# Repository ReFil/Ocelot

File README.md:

# Ocelot
Ocelot universal vehicle interface

This is an in progress project aimed at creating a universal set of hardware intended to allow autonomous driving.
The hardware consists of a fly by wire pedal interceptor, a universal cruise controls emulator, reverse engineered white panda and black panda, canbus gateway board for iboosters or corolla EPS controllers and an interface board that ties everythign together
In the future we plan on a cable throttle actuator and a speed and pedal sensor to allow for fitting on cars without any electronics at all.

The software for most of the modules is based off the comma.ai panda firmware to take advantage of the safety and updating over CAN bus

Any user of this software/hardsware shall indemnify and hold harmless Willow Herring. and their associates from and against all allegations, claims, actions, suits, demands, damages, liabilities, obligations, losses, settlements, judgments, costs and expenses (including without limitation attorneys’ fees and costs) which arise out of, relate to or result from any use of this software by user.

THIS IS ALPHA QUALITY HARDWARE FOR RESEARCH PURPOSES ONLY. THIS IS NOT A PRODUCT. YOU ARE RESPONSIBLE FOR COMPLYING WITH LOCAL LAWS AND REGULATIONS. NO WARRANTY EXPRESSED OR IMPLIED
I AM NOT RESPONSIBLE FOR WORLD WAR 3, YOUR HOUSE BURNING DOWN OR YOU GETTING FIRED BECAUSE YOUR CAR BROKE DOWN ON THE WAY TO WORK, BY USING THIS HARDWARE/SOFTWARE YOU ASSUME RESPONSIBILITY FOR ALL CONSEQUENCES.

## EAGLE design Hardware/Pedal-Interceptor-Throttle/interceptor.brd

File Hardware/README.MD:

Hardware

The hardware is designed to be as easy to use as possible.

All can bus connections are made using molex mini50 4 pin connectors with A polarisation
The pinout is 12V CANH CANL GND from pin 1-4

The CAN interface board connects everything together, compatible with white, grey and black panda as well as c2

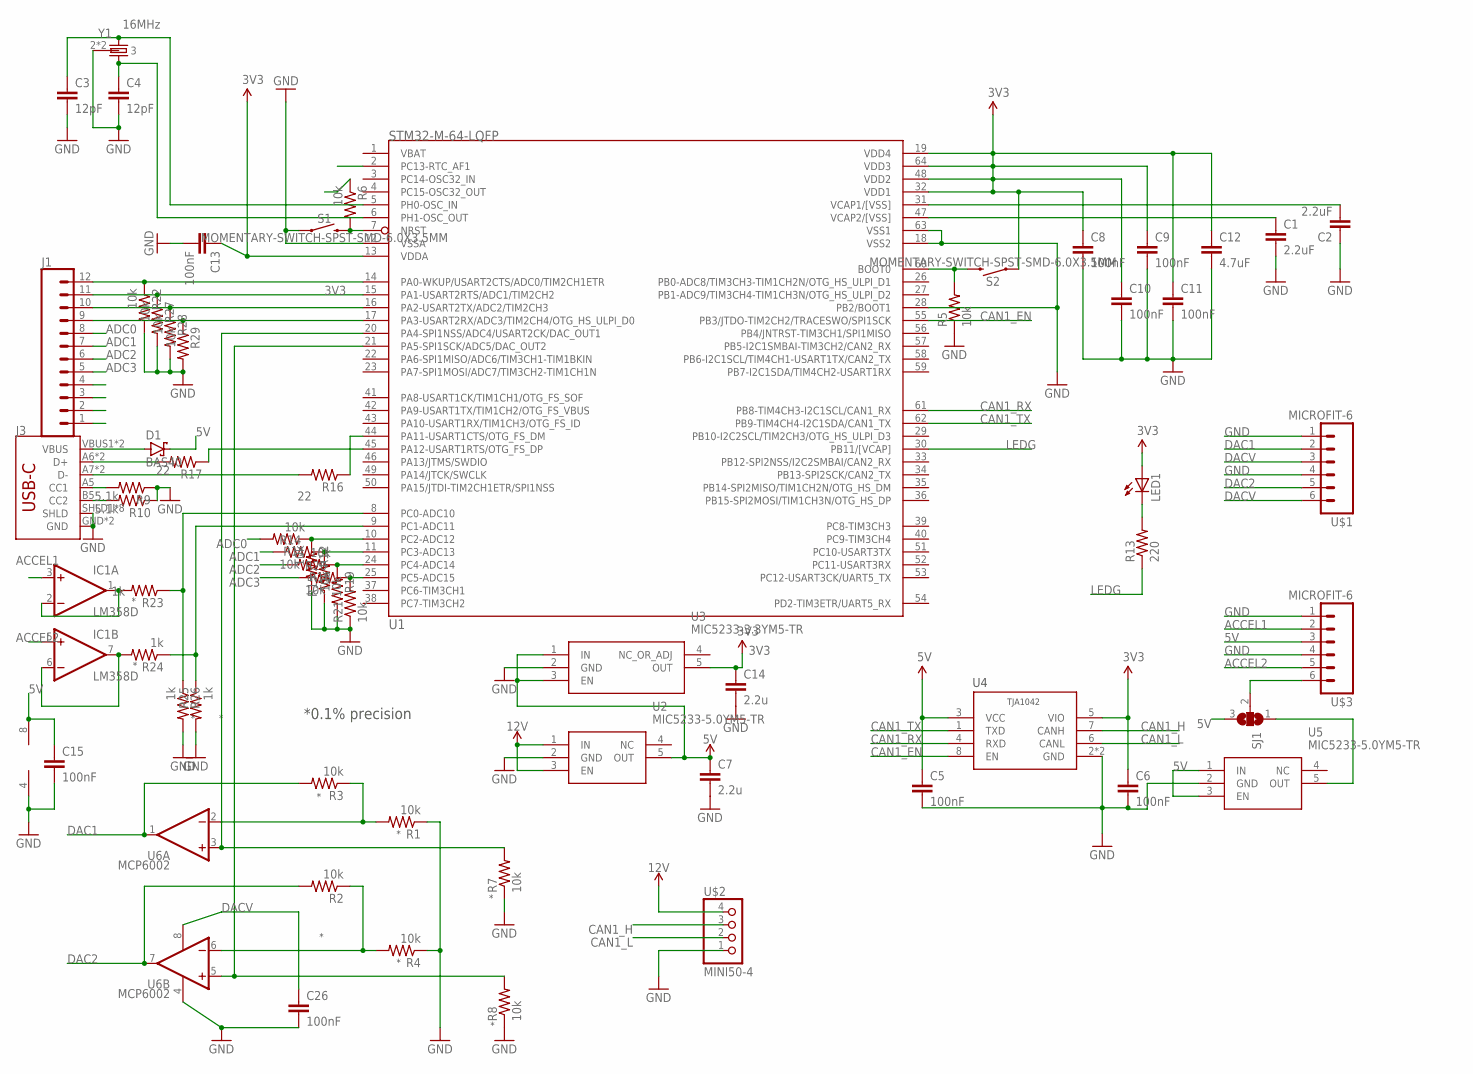
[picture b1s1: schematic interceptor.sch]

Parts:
C1, C2: 2.2uF; 0603-C
C3, C4: 12pF; 0603-C
C5, C6, C8, C9, C10, C11, C13, C15, C26: 100nF; 0603-C
C7, C14: 2.2u; C0603
C12: 4.7uF; 0603-C
D1: BAS40; SOT23
IC1: LM358D; SO08
J1: CONN_12; 1X12
J3: USB-C-BREAKOUT_SPARKFUN-CONNECTORS_USB_C16PIN; USB-C-BREAKOUT_SPARKFUN-CONNECTORS_USB-C-16P
LED1: LEDCHIPLED_0805; CHIPLED_0805
R1, R2, R3, R4, R5, R6, R7, R8, R11, R12, R14, R15, R18, R19, R20, R21, R22, R27, R28, R29: 10k; 0402-R
R9, R10: 5.1k; 0402-R
R13: 220; 0402-R
R16, R17: 22; 0402-R
R23, R24, R25, R26: 1k; 0402-R
S1, S2: MOMENTARY-SWITCH-SPST-SMD-6.0X3.5MM; TACTILE_SWITCH_SMD_6.0X3.5MM
SJ1: SJ2W; SJ_2
U1: STM32-M-64-LQFP; LQFP64
U2, U5: MIC5233-5.0YM5-TR; SOT95P280X145-5N
U3: MIC5233-3.3YM5-TR; SOT95P280X145-5N
U4: TJA1042HVSON; HVSON8
U6: MCP6002; SO08
U$1, U$3: MICROFIT-6
U$2: MINI50-4; MINI50
Y1: 16MHz; XTAL-3.2X2.5

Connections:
3V3: C6.1, C8.1, C9.1, C10.1, C11.1, C12.1, C13.1, C14.1, LED1.A, R6.1, S2.1, U1.13 (VDDA), U1.19 (VDD4), U1.32 (VDD1), U1.48 (VDD2), U1.64 (VDD3), U3.5 (OUT), U4.5 (VIO)
5V: C5.1, C7.1, C15.1, D1.3 (C), IC1.8 (V+), SJ1.3, U2.5 (OUT), U3.1 (IN), U3.3 (EN), U4.3 (VCC), U5.1 (IN), U5.3 (EN), U$3.3
12V: U2.1 (IN), U2.3 (EN), U$2.4 (1)
ACCEL1: IC1.3 (+IN), U$3.2
ACCEL2: IC1.5 (+IN), U$3.5
ADC0: J1.8, R11.2
ADC1: J1.7, R14.1
ADC2: J1.6, R18.2
ADC3: J1.5, R20.1
CAN1_EN: U1.55 (PB3/JTDO-TIM2CH2/TRACESWO/SPI1SCK), U4.8 (EN)
CAN1_H: U4.7 (CANH), U$2.3 (2)
CAN1_L: U4.6 (CANL), U$2.2 (3)
CAN1_RX: U1.61 (PB8-TIM4CH3-I2C1SCL/CAN1_RX), U4.4 (RXD)
CAN1_TX: U1.62 (PB9-TIM4CH4-I2C1SDA/CAN1_TX), U4.1 (TXD)
DAC1: R3.2, U6.1 (OUT), U$1.2
DAC2: R2.2, U6.7 (OUT), U$1.5
DACV: C26.1, U6.8 (V+), U$1.3, U$1.6
GND: C1.2, C2.1, C3.2, C4.2, C5.2, C6.2, C7.2, C8.2, C9.2, C10.2, C11.2, C12.2, C13.2, C14.2, C15.2, C26.2, IC1.4 (V-), J3.GND, J3.GND2 (GND), J3.SHLD1 (SHLD), J3.SHLD2 (SHLD), J3.SHLD3 (SHLD), J3.SHLD4 (SHLD), J3.SHLD5 (SHLD), J3.SHLD6 (SHLD), J3.SHLD7 (SHLD), J3.SHLD8 (SHLD), R1.1, R4.1, R5.1, R7.1, R8.1, R9.1, R10.1, R12.2, R15.1, R19.2, R21.1, R22.2, R25.2, R26.2, R27.2, R28.2, R29.2, S1.1, U1.12 (VSSA), U1.18 (VSS2), U1.28 (PB2/BOOT1), U1.63 (VSS1), U2.2 (GND), U3.2 (GND), U4.2 (GND), U4.PAD (GND), U5.2 (GND), U6.4 (V-), U$1.1, U$1.4, U$2.1 (4), U$3.1, U$3.4, Y1.2 (3), Y1.4 (3)
LEDG: R13.1, U1.30 (PB11/[VCAP])
unnamed: C3.1, U1.5 (PH0-OSC_IN), Y1.1
unnamed: R16.1, U1.44 (PA11-USART1CTS/OTG_FS_DM)
unnamed: C4.1, U1.6 (PH1-OSC_OUT), Y1.3 (2)
unnamed: R17.1, U1.45 (PA12-USART1RTS/OTG_FS_DP)
unnamed: J3.A7 (D-), J3.B7 (D-), R16.2
unnamed: J3.A6 (D+), J3.B6 (D+), R17.2
unnamed: R5.2, S2.2, U1.60 (BOOT0)
unnamed: J3.A5 (CC1), R9.2
unnamed: J3.B5 (CC2), R10.2
unnamed: R6.2, S1.2, U1.7 (NRST)
unnamed: D1.1 (A), J3.VBUS1 (VBUS), J3.VBUS2 (VBUS)
unnamed: SJ1.2, U$3.6
unnamed: IC1.1 (OUT), IC1.2 (-IN), R23.2
unnamed: SJ1.1, U5.5 (OUT)
unnamed: IC1.6 (-IN), IC1.7 (OUT), R24.2
unnamed: R11.1, R12.1, U1.10 (PC2-ADC12)
unnamed: R7.2, U1.20 (PA4-SPI1NSS/ADC4/USART2CK/DAC_OUT1), U6.3 (+IN)
unnamed: R8.2, U1.21 (PA5-SPI1SCK/ADC5/DAC_OUT2), U6.5 (+IN)
unnamed: R14.2, R15.2, U1.11 (PC3-ADC13)
unnamed: R18.1, R19.1, U1.24 (PC4-ADC14)
unnamed: R1.2, R3.1, U6.2 (-IN)
unnamed: R2.1, R4.2, U6.6 (-IN)
unnamed: R20.2, R21.2, U1.25 (PC5-ADC15)
unnamed: LED1.C, R13.2
unnamed: J1.9, R29.1, U1.17 (PA3-USART2RX/ADC3/TIM2CH4/OTG_HS_ULPI_D0)
unnamed: J1.10, R28.1, U1.16 (PA2-USART2TX/ADC2/TIM2CH3)
unnamed: J1.11, R27.1, U1.15 (PA1-USART2RTS/ADC1/TIM2CH2)
unnamed: J1.12, R22.1, U1.14 (PA0-WKUP/USART2CTS/ADC0/TIM2CH1ETR)
unnamed: R23.1, R26.1, U1.8 (PC0-ADC10)
unnamed: R24.1, R25.1, U1.9 (PC1-ADC11)
VCAP1: C2.2, U1.31 (VCAP1/[VSS])
VCAP2: C1.1, U1.47 (VCAP2/[VSS])

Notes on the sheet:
*0.1% precision

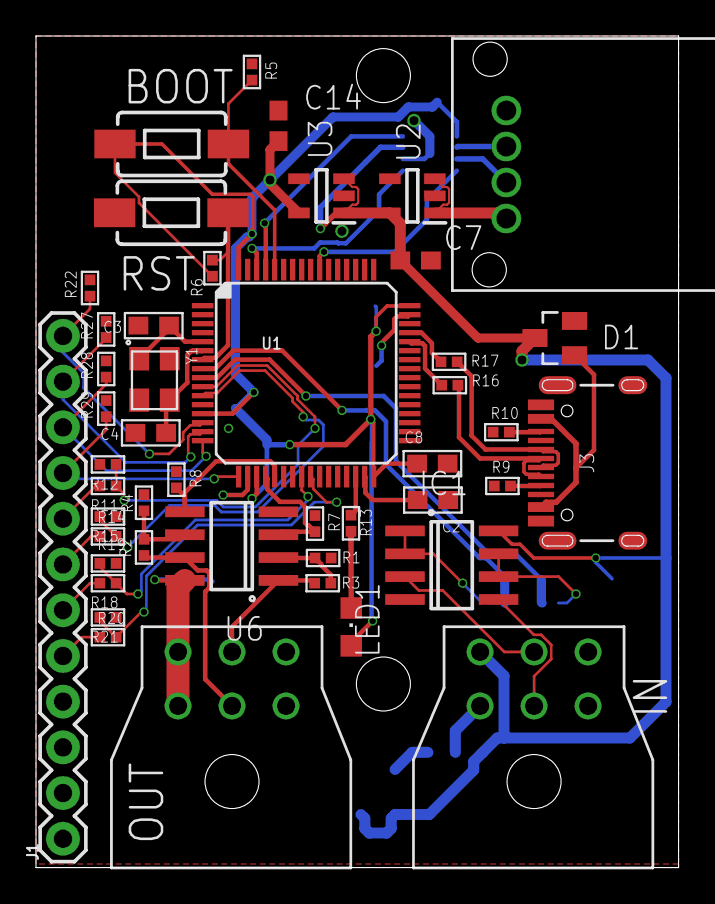
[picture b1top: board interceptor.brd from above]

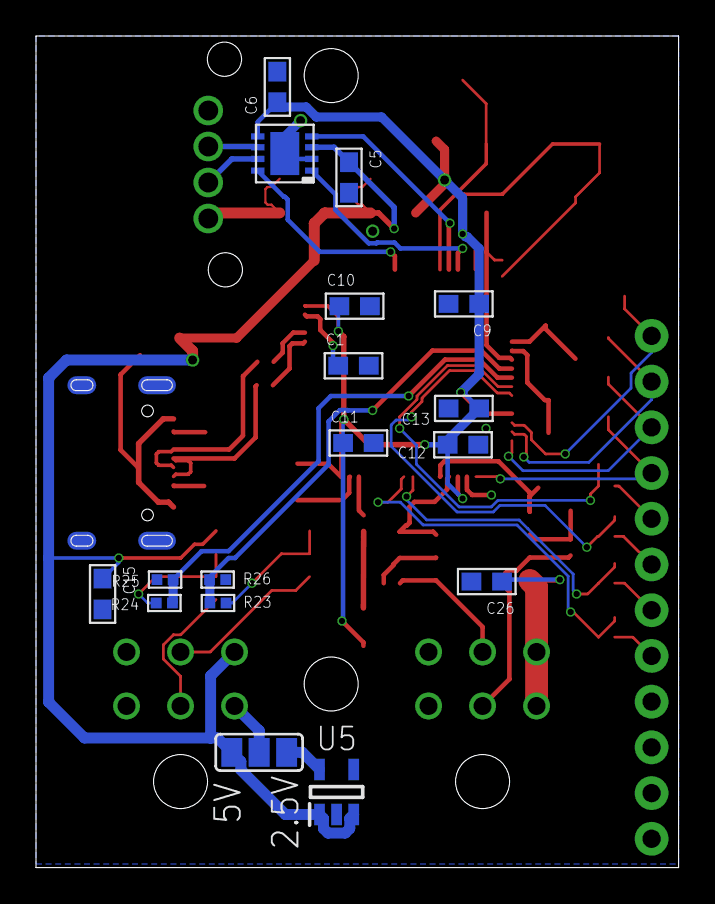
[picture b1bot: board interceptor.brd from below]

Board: 2 copper layers, 35.7 x 46.2 mm, 63 parts (17 on the bottom side), 51 nets.

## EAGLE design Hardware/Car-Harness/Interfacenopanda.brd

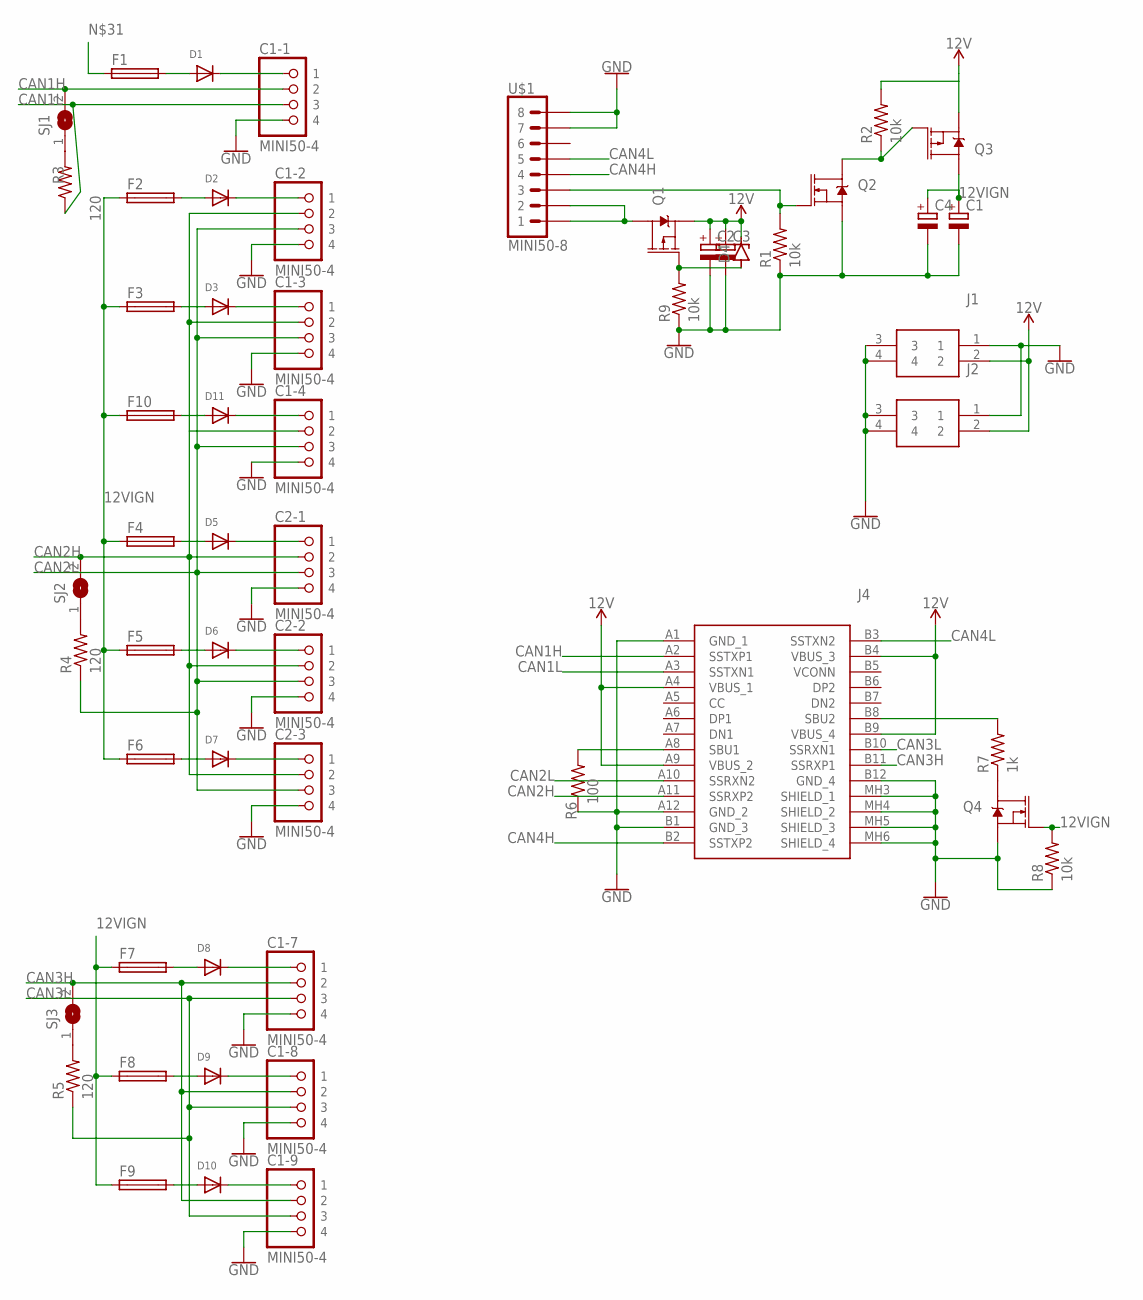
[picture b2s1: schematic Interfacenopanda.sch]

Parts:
C1, C2: CPOL-EU153CLV-1010; 153CLV-1010
C1-1, C1-2, C1-3, C1-4, C1-7, C1-8, C1-9, C2-1, C2-2, C2-3: MINI50-4; MINI50
C3, C4: CPOL-EU153CLV-0505; 153CLV-0505
D1, D2, D3, D5, D6, D7, D8, D9, D10, D11: DIODESOD-323F; SOD-323F
D4: ZENER_DO-219-AB(SOD123F); SODFL3718X115
F1, F2, F3, F4, F5, F6, F7, F8, F9, F10: FUSE_CHIP-1206(3216-METRIC); FUSC3215X82N
J1, J2: 34912-8020; 0349128020
J4: 632722110112
Q1, Q3: 6.5A/20V/35mΩ; SO08
Q2, Q4: 5.8A/30V/35mΩ; SOT23-3
R1, R2, R8, R9: 10k; 0402-R
R3, R4, R5: 120; 0402-R
R6: 100; 0402-R
R7: 1k; 0402-R
SJ1, SJ2, SJ3: SJ
U$1: MINI50-8

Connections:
12V: C2.+, C3.+, D4.2 (C), J1.2, J2.2, J4.A4 (VBUS_1), J4.A9 (VBUS_2), J4.B4 (VBUS_3), J4.B9 (VBUS_4), Q1.1 (S), Q1.2 (S), Q1.3 (S), Q3.1 (S), Q3.2 (S), Q3.3 (S), R2.2
12VIGN: C1.+, C4.+, F2.1, F3.1, F4.1, F5.1, F6.1, F7.1, F8.1, F9.1, F10.1, Q3.5 (D), Q3.6 (D), Q3.7 (D), Q3.8 (D), Q4.1 (G), R8.2
CAN1H: C1-1.3 (2), J4.A2 (SSTXP1), SJ1.2
CAN1L: C1-1.2 (3), J4.A3 (SSTXN1), R3.1
CAN2H: C1-2.3 (2), C1-3.3 (2), C1-4.3 (2), C2-1.3 (2), C2-2.3 (2), C2-3.3 (2), J4.A11 (SSRXP2), SJ2.2
CAN2L: C1-2.2 (3), C1-3.2 (3), C1-4.2 (3), C2-1.2 (3), C2-2.2 (3), C2-3.2 (3), J4.A10 (SSRXN2), R4.1
CAN3H: C1-7.3 (2), C1-8.3 (2), C1-9.3 (2), J4.B11 (SSRXP1), SJ3.2
CAN3L: C1-7.2 (3), C1-8.2 (3), C1-9.2 (3), J4.B10 (SSRXN1), R5.1
CAN4H: J4.B2 (SSTXP2), U$1.P$4 (4)
CAN4L: J4.B3 (SSTXN2), U$1.P$5 (5)
GND: C1.-, C1-1.1 (4), C1-2.1 (4), C1-3.1 (4), C1-4.1 (4), C1-7.1 (4), C1-8.1 (4), C1-9.1 (4), C2.-, C2-1.1 (4), C2-2.1 (4), C2-3.1 (4), C3.-, C4.-, J1.1, J1.3, J1.4, J2.1, J2.3, J2.4, J4.A1 (GND_1), J4.A12 (GND_2), J4.B1 (GND_3), J4.B12 (GND_4), J4.MH3 (SHIELD_1), J4.MH4 (SHIELD_2), J4.MH5 (SHIELD_3), J4.MH6 (SHIELD_4), Q2.2 (S), Q4.2 (S), R1.1, R6.1, R8.1, R9.1, U$1.P$7 (7), U$1.P$8 (8)
unnamed: D1.A, F1.2
unnamed: C1-1.4 (1), D1.C
unnamed: D2.A, F2.2
unnamed: C1-2.4 (1), D2.C
unnamed: D3.A, F3.2
unnamed: C1-3.4 (1), D3.C
unnamed: R3.2, SJ1.1
unnamed: D5.A, F4.2
unnamed: C2-1.4 (1), D5.C
unnamed: Q1.5 (D), Q1.6 (D), Q1.7 (D), Q1.8 (D), U$1.P$1 (1), U$1.P$2 (2)
unnamed: D6.A, F5.2
unnamed: Q2.1 (G), R1.2, U$1.P$3 (3)
unnamed: C2-2.4 (1), D6.C
unnamed: D7.A, F6.2
unnamed: Q2.3 (D), Q3.4 (G), R2.1
unnamed: C2-3.4 (1), D7.C
unnamed: R4.2, SJ2.1
unnamed: D8.A, F7.2
unnamed: C1-7.4 (1), D8.C
unnamed: D9.A, F8.2
unnamed: C1-8.4 (1), D9.C
unnamed: D10.A, F9.2
unnamed: C1-9.4 (1), D10.C
unnamed: R5.2, SJ3.1
unnamed: J4.B8 (SBU2), R7.2
unnamed: D4.1 (A), Q1.4 (G), R9.2
unnamed: D11.A, F10.2
unnamed: C1-4.4 (1), D11.C
unnamed: Q4.3 (D), R7.1
unnamed: J4.A8 (SBU1), R6.2

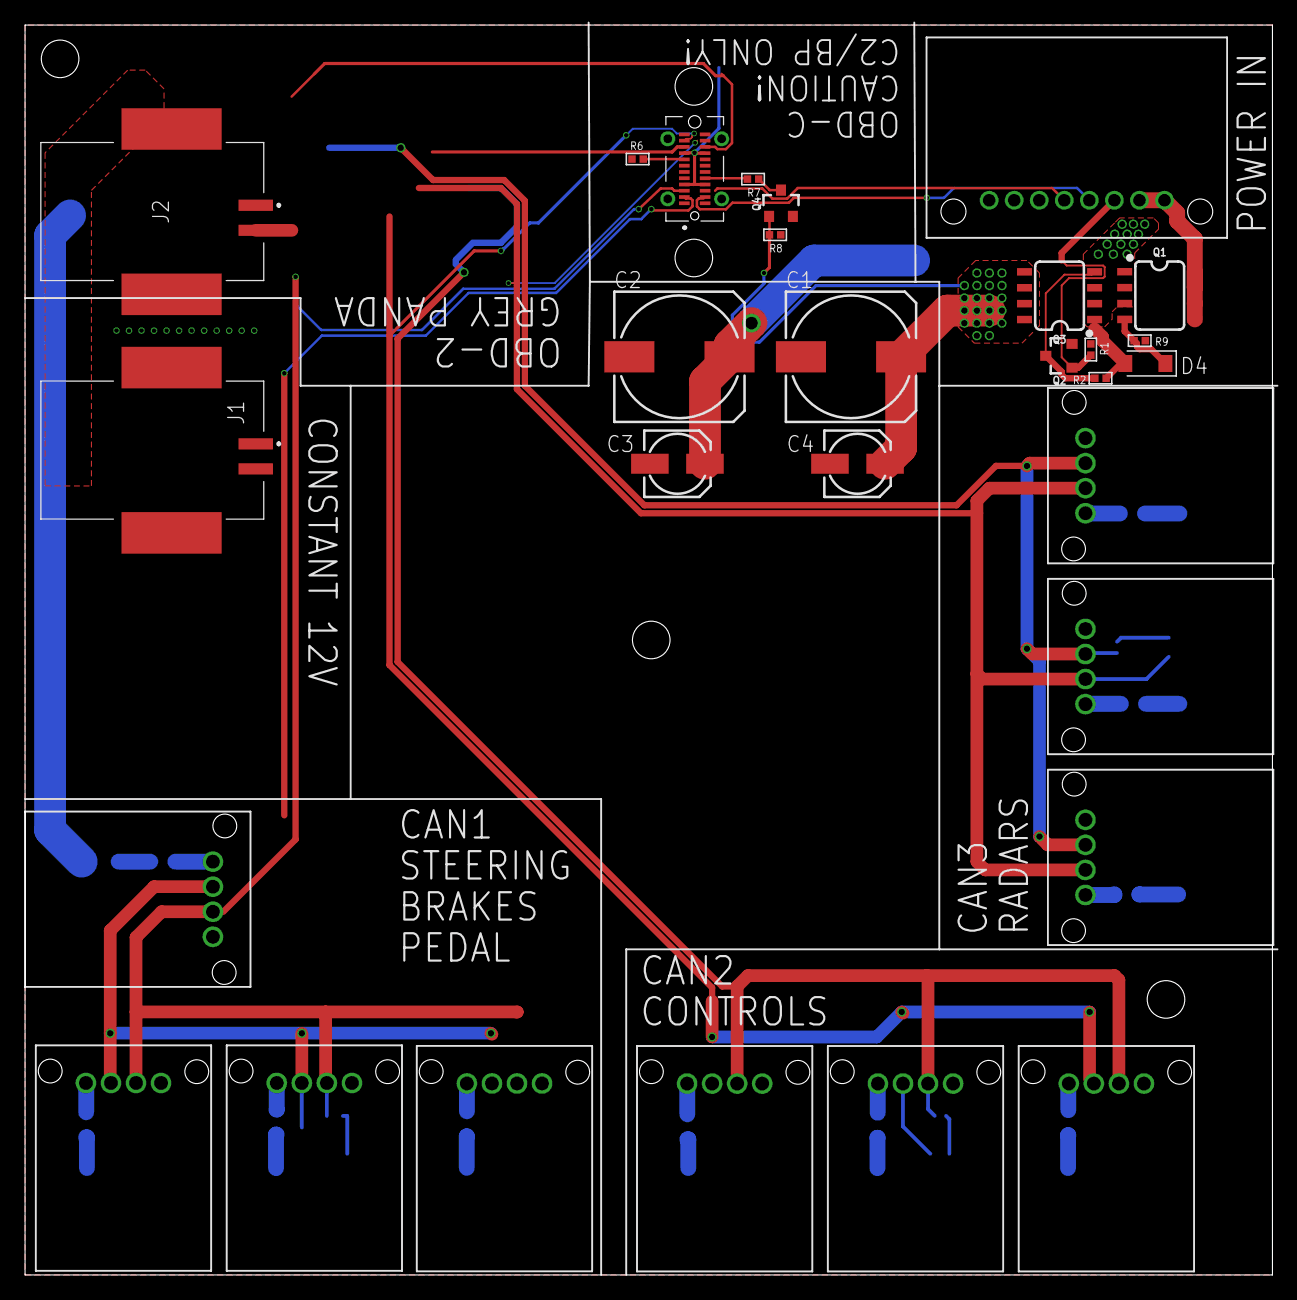
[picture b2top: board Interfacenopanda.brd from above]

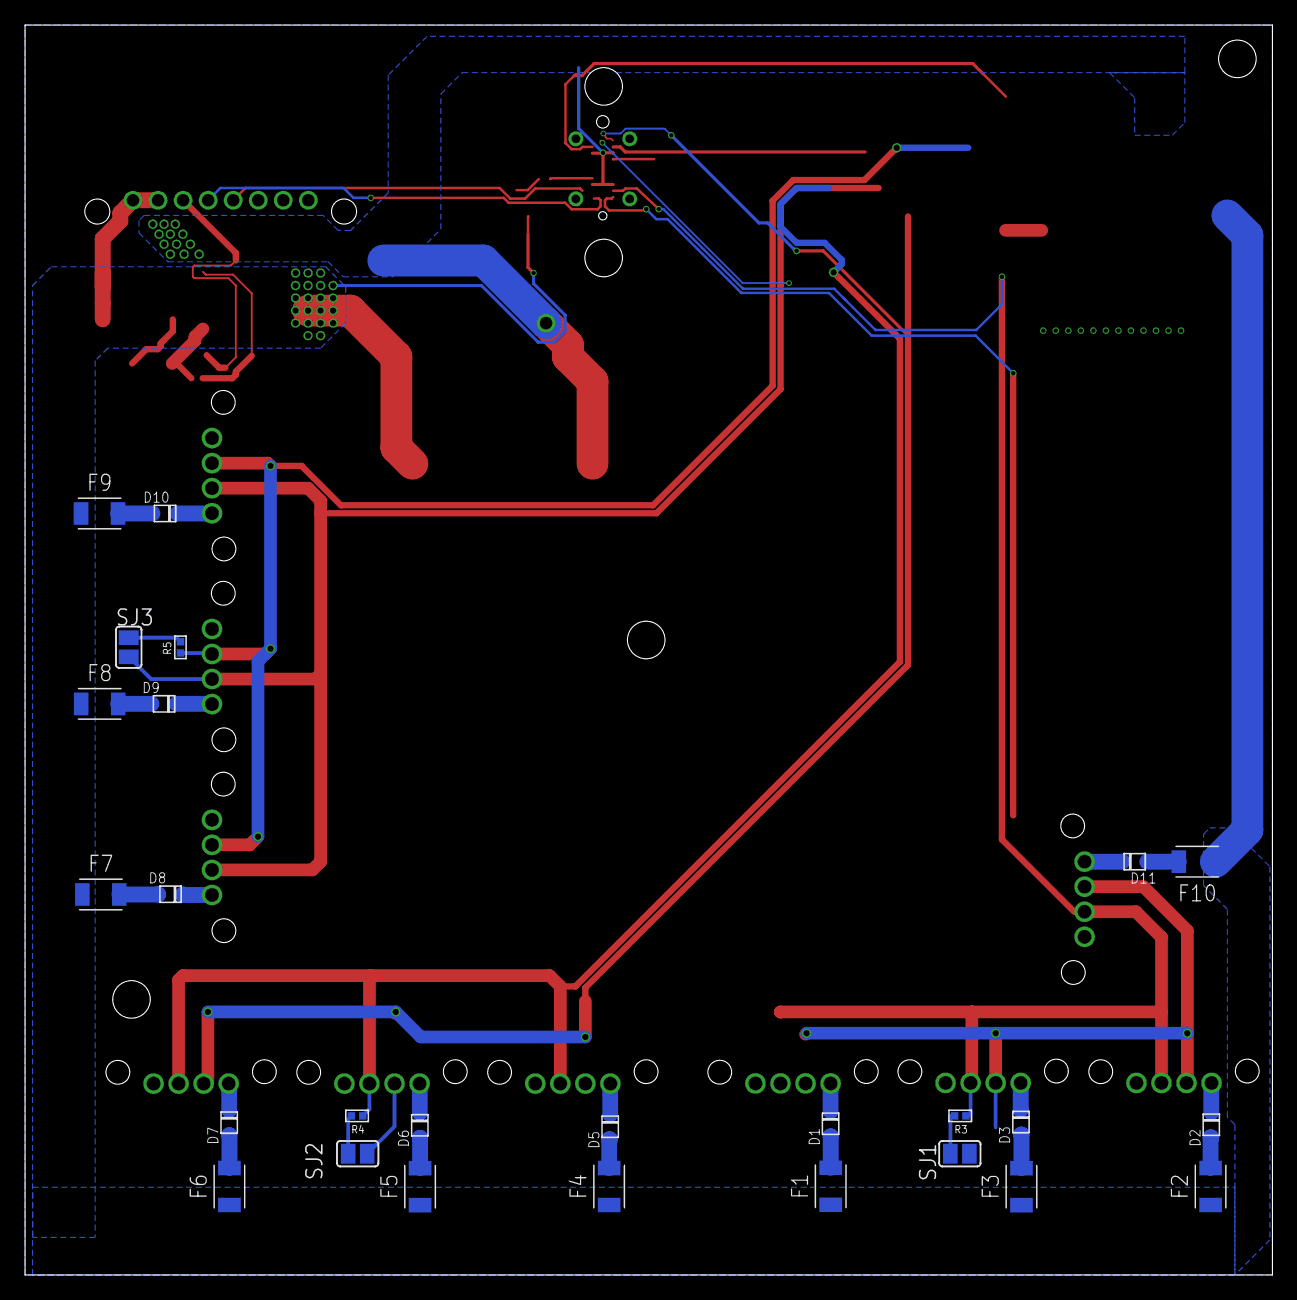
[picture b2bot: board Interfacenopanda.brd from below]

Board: 2 copper layers, 99.6 x 99.8 mm, 55 parts (26 on the bottom side), 41 nets.

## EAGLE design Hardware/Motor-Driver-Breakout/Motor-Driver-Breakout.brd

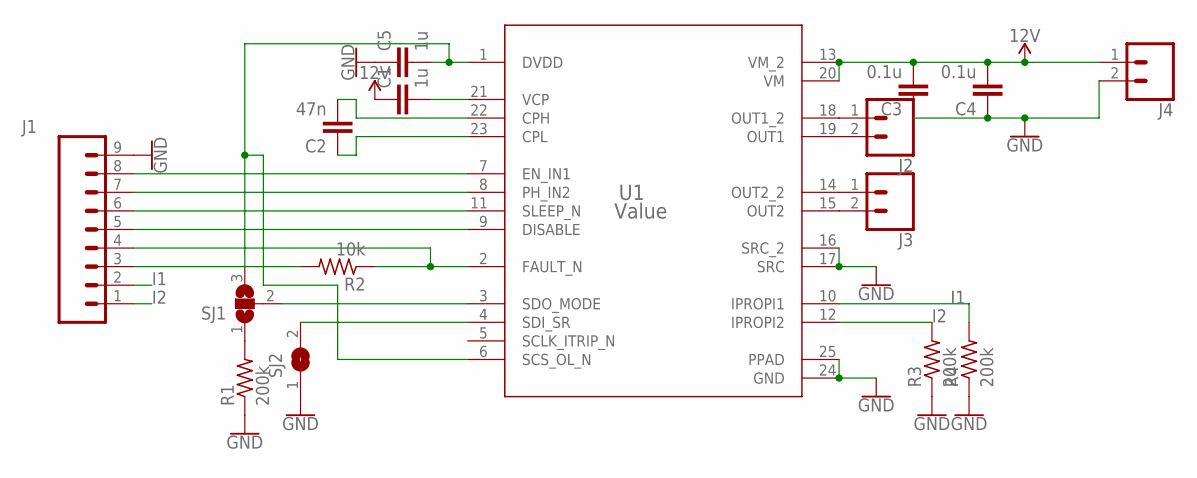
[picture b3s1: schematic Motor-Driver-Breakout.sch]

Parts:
C1, C5: 1u; 0603-C
C2: 47n; 0603-C
C3, C4: 0.1u; 0603-C
J1: CONN_09; 1X09
J2, J3, J4: CONN_02; 1X02
R1, R3, R4: 200k; 0603-R
R2: 10k; 0603-R
SJ1: SJ2W; SJ_2
SJ2: SJ
U1: Value; PWP0024J_N

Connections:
12V: C1.1, C3.2, C4.2, J4.1, U1.13 (VM_2), U1.20 (VM)
GND: C3.1, C4.1, C5.1, J1.9, J4.2, R1.1, R3.1, R4.1, SJ2.1, U1.16 (SRC_2), U1.17 (SRC), U1.24 (GND), U1.25 (PPAD)
I1: J1.2, R4.2, U1.10 (IPROPI1)
I2: J1.1, R3.2, U1.12 (IPROPI2)
unnamed: SJ1.2, U1.3 (SDO_MODE)
unnamed: R1.2, SJ1.1
unnamed: J1.4, R2.1, U1.2 (FAULT_N)
unnamed: C5.2, SJ1.3, U1.1 (DVDD), U1.6 (SCS_OL_N)
unnamed: C1.2, U1.21 (VCP)
unnamed: C2.2, U1.22 (CPH)
unnamed: C2.1, U1.23 (CPL)
unnamed: J2.1, U1.18 (OUT1_2)
unnamed: SJ2.2, U1.4 (SDI_SR)
unnamed: J2.2, U1.19 (OUT1)
unnamed: J1.6, U1.11 (SLEEP_N)
unnamed: J1.8, U1.7 (EN_IN1)
unnamed: J1.7, U1.8 (PH_IN2)
unnamed: J1.5, U1.9 (DISABLE)
unnamed: J1.3, R2.2
unnamed: J3.1, U1.14 (OUT2_2)
unnamed: J3.2, U1.15 (OUT2)

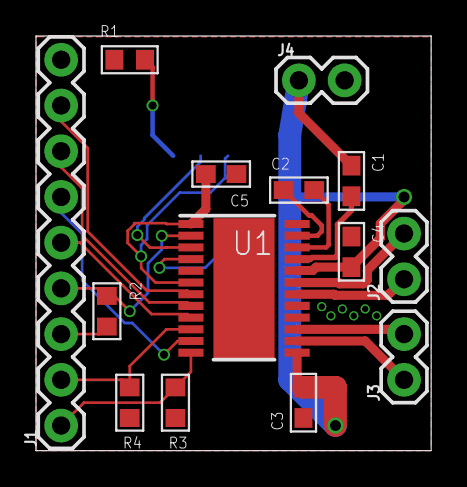
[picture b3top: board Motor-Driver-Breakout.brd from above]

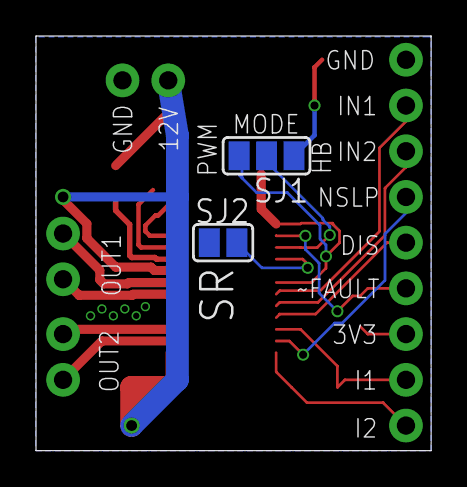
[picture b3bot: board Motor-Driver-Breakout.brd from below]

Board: 2 copper layers, 22.0 x 23.0 mm, 16 parts (2 on the bottom side), 21 nets.

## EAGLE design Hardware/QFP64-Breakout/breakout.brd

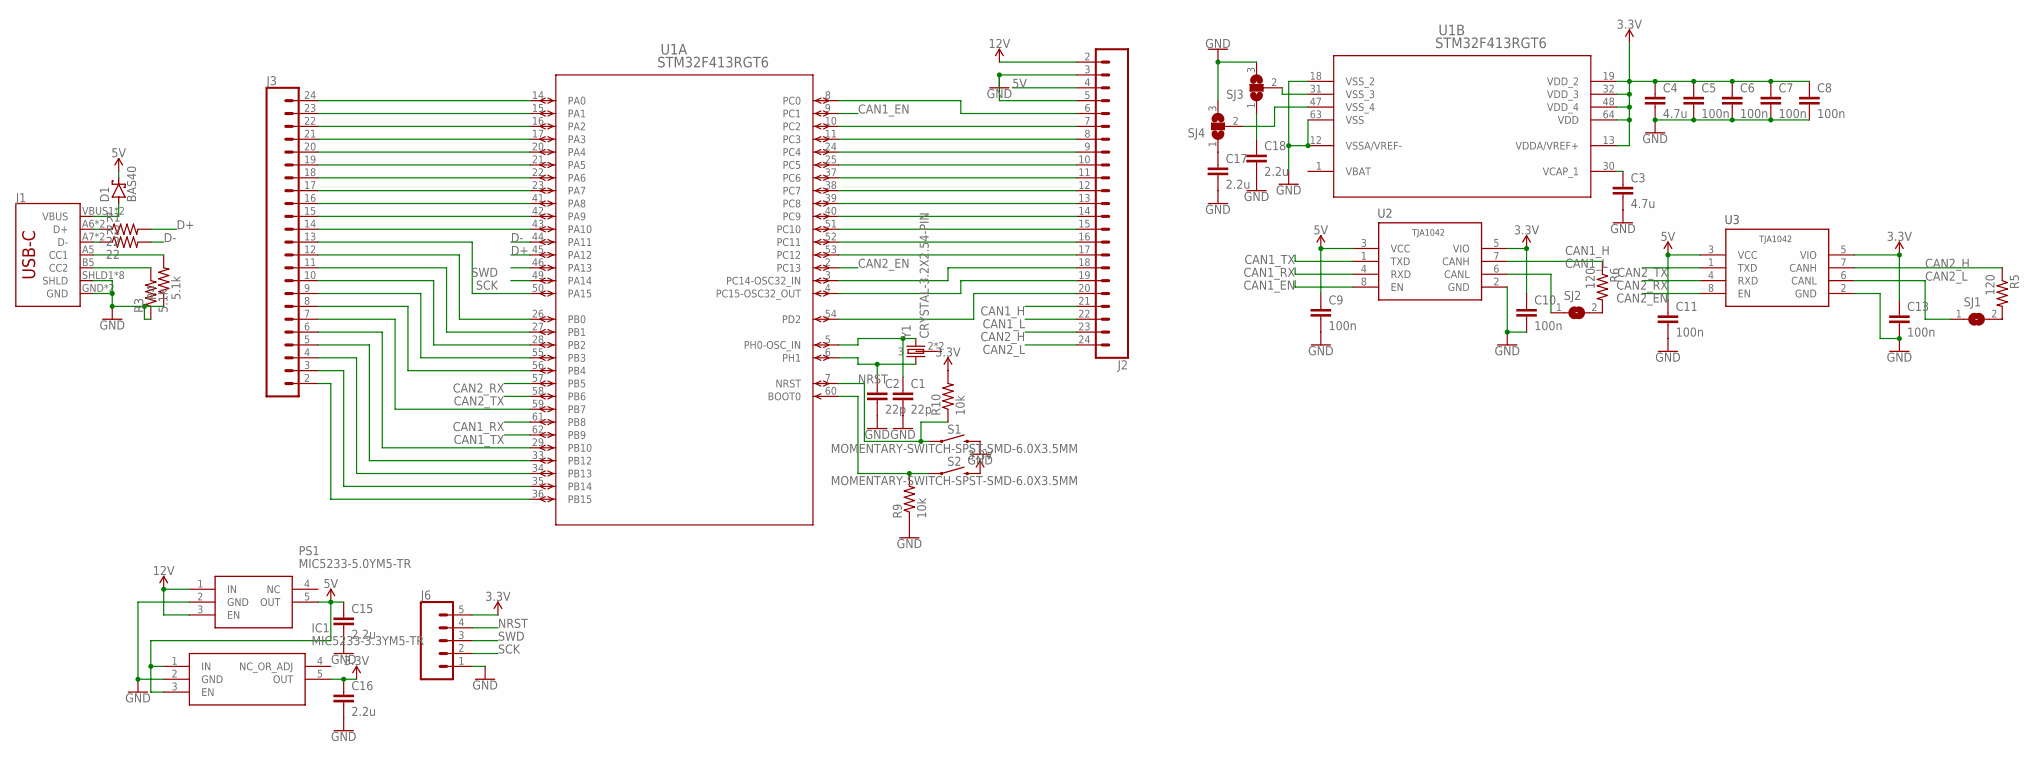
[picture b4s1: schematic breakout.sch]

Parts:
C1, C2: 22p; 0603-C
C3, C4: 4.7u; 0603-C
C5, C6, C7, C8, C9, C10, C11, C13: 100n; 0603-C
C15, C16, C17, C18: 2.2u; 0603-C
D1: BAS40; SOT23
IC1: MIC5233-3.3YM5-TR; SOT95P280X145-5N
J1: USB-C-BREAKOUT_SPARKFUN-CONNECTORS_USB_C16PIN; USB-C-BREAKOUT_SPARKFUN-CONNECTORS_USB-C-16P
J2, J3: CONN_23; 1X23
J6: CONN_05; 1X05
PS1: MIC5233-5.0YM5-TR; SOT95P280X145-5N
R1, R2: 22; 0402-R
R3, R4: 5.1k; 0402-R
R5, R6: 120; 0402-R
R9, R10: 10k; 0402-R
S1, S2: MOMENTARY-SWITCH-SPST-SMD-6.0X3.5MM; TACTILE_SWITCH_SMD_6.0X3.5MM
SJ1, SJ2: SJ
SJ3, SJ4: SJ2W; SJ_2
U1: STM32F413RGT6; LQFP64-10X10MM
U2, U3: TJA1042; NXP_SEMICONDUCTORS_TJA1042T-3-CM_118_0
Y1: CRYSTAL-3.2X2.54-PIN; XTAL-3.2X2.5

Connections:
3.3V: C4.1, C5.1, C6.1, C7.1, C8.1, C10.1, C13.1, C16.1, IC1.5 (OUT), J6.5, R10.2, S2.2, U1.13 (VDDA/VREF+), U1.19 (VDD_2), U1.32 (VDD_3), U1.48 (VDD_4), U1.64 (VDD), U2.5 (VIO), U3.5 (VIO)
5V: C9.1, C11.1, C15.1, D1.3 (C), IC1.1 (IN), IC1.3 (EN), J2.4, PS1.5 (OUT), U2.3 (VCC), U3.3 (VCC)
12V: J2.2, PS1.1 (IN), PS1.3 (EN)
CAN1_EN: U1.9 (PC1), U2.8 (EN)
CAN1_H: J2.21, R6.1, U2.7 (CANH)
CAN1_L: J2.22, SJ2.1, U2.6 (CANL)
CAN1_RX: U1.61 (PB8), U2.4 (RXD)
CAN1_TX: U1.62 (PB9), U2.1 (TXD)
CAN2_EN: U1.2 (PC13), U3.8 (EN)
CAN2_H: J2.23, R5.1, U3.7 (CANH)
CAN2_L: J2.24, SJ1.1, U3.6 (CANL)
CAN2_RX: U1.57 (PB5), U3.4 (RXD)
CAN2_TX: U1.58 (PB6), U3.1 (TXD)
D+: R1.2, U1.45 (PA12)
D-: R2.2, U1.44 (PA11)
GND: C1.2, C2.2, C3.2, C4.2, C5.2, C6.2, C7.2, C8.2, C9.2, C10.2, C11.2, C13.2, C15.2, C16.2, C17.2, C18.2, IC1.2 (GND), J1.GND, J1.GND2 (GND), J1.SHLD1 (SHLD), J1.SHLD2 (SHLD), J1.SHLD3 (SHLD), J1.SHLD4 (SHLD), J1.SHLD5 (SHLD), J1.SHLD6 (SHLD), J1.SHLD7 (SHLD), J1.SHLD8 (SHLD), J2.3, J2.5, J6.1, PS1.2 (GND), R3.1, R4.1, R9.1, S1.2, SJ3.3, SJ4.3, U1.12 (VSSA/VREF-), U1.18 (VSS_2), U1.63 (VSS), U2.2 (GND), U3.2 (GND)
unnamed: C1.1, U1.5 (PH0-OSC_IN), Y1.3 (2)
unnamed: C2.1, U1.6 (PH1), Y1.1
unnamed: J3.24, U1.14 (PA0)
unnamed: J3.23, U1.15 (PA1)
unnamed: D1.1 (A), J1.VBUS1 (VBUS), J1.VBUS2 (VBUS)
unnamed: J1.A5 (CC1), R4.2
unnamed: J1.B5 (CC2), R3.2
unnamed: C17.1, SJ4.1
unnamed: R9.2, S2.1, U1.60 (BOOT0)
unnamed: J1.A6 (D+), J1.B6 (D+), R1.1
unnamed: J1.A7 (D-), J1.B7 (D-), R2.1
unnamed: R5.2, SJ1.2
unnamed: C3.1, U1.30 (VCAP_1)
unnamed: J3.22, U1.16 (PA2)
unnamed: SJ3.2, U1.31 (VSS_3)
unnamed: SJ4.2, U1.47 (VSS_4)
unnamed: C18.1, SJ3.1
unnamed: J3.21, U1.17 (PA3)
unnamed: J3.20, U1.20 (PA4)
unnamed: J3.19, U1.21 (PA5)
unnamed: J3.18, U1.22 (PA6)
unnamed: J3.17, U1.23 (PA7)
unnamed: J3.16, U1.41 (PA8)
unnamed: J3.15, U1.42 (PA9)
unnamed: J3.14, U1.43 (PA10)
unnamed: J3.13, U1.50 (PA15)
unnamed: J3.12, U1.26 (PB0)
unnamed: J3.11, U1.27 (PB1)
unnamed: J3.10, U1.28 (PB2)
unnamed: J3.9, U1.55 (PB3)
unnamed: J3.8, U1.56 (PB4)
unnamed: J3.7, U1.59 (PB7)
unnamed: J3.6, U1.29 (PB10)
unnamed: J3.5, U1.33 (PB12)
unnamed: J3.4, U1.34 (PB13)
unnamed: J3.3, U1.35 (PB14)
unnamed: J3.2, U1.36 (PB15)
unnamed: J2.20, U1.54 (PD2)
unnamed: J2.19, U1.4 (PC15-OSC32_OUT)
unnamed: J2.18, U1.3 (PC14-OSC32_IN)
unnamed: J2.17, U1.53 (PC12)
unnamed: J2.16, U1.52 (PC11)
unnamed: J2.15, U1.51 (PC10)
unnamed: J2.14, U1.40 (PC9)
unnamed: J2.13, U1.39 (PC8)
unnamed: J2.12, U1.38 (PC7)
unnamed: J2.11, U1.37 (PC6)
unnamed: J2.10, U1.25 (PC5)
unnamed: J2.9, U1.24 (PC4)
unnamed: J2.8, U1.11 (PC3)
unnamed: J2.7, U1.10 (PC2)
unnamed: J2.6, U1.8 (PC0)
unnamed: R6.2, SJ2.2
NRST: J6.4, R10.1, S1.1, U1.7 (NRST)
SCK: J6.2, U1.49 (PA14)
SWD: J6.3, U1.46 (PA13)
VBAT: U1.1 (VBAT)

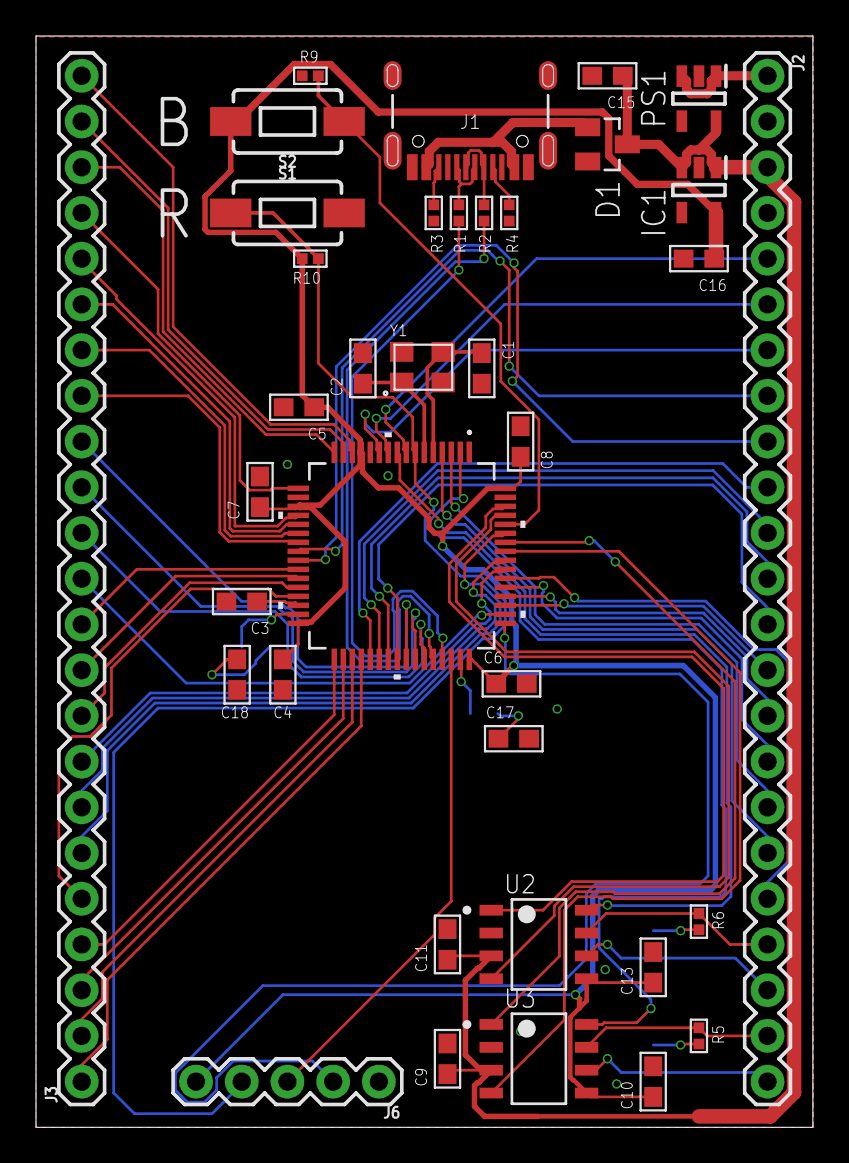
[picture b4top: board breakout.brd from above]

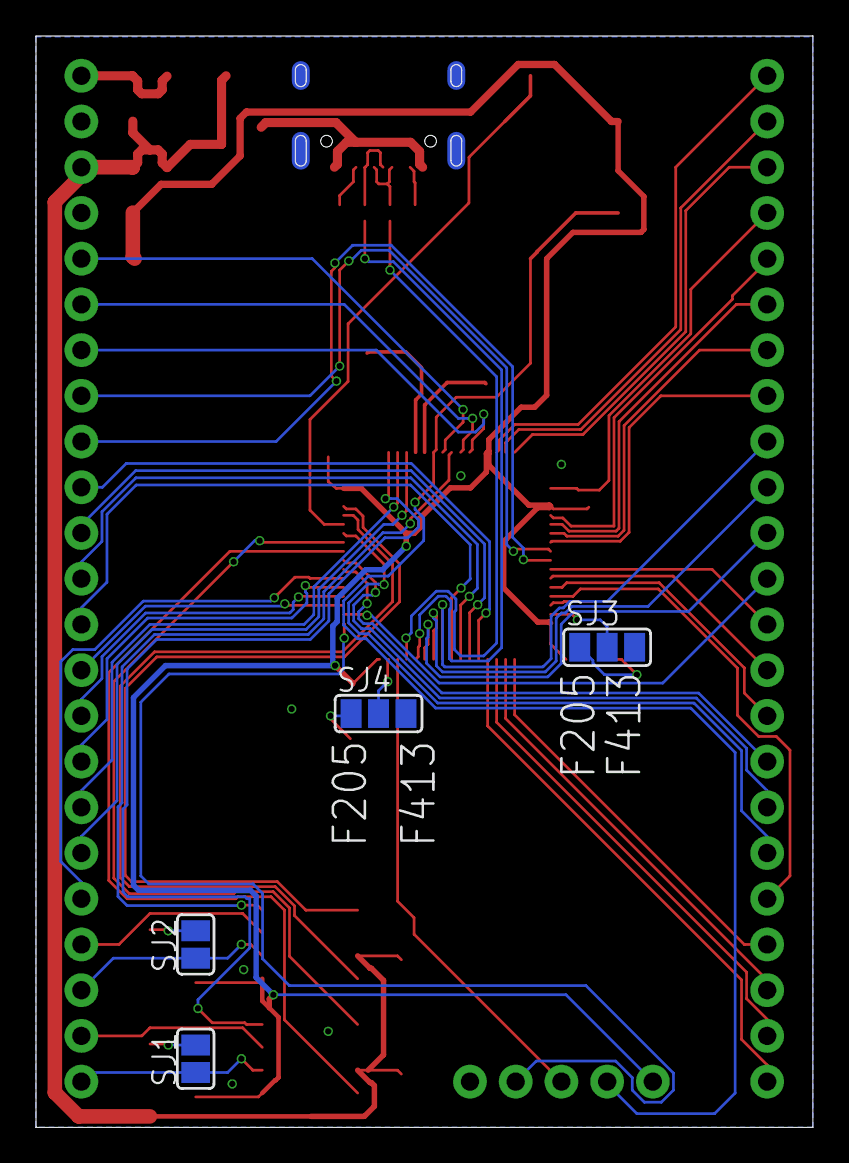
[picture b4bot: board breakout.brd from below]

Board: 2 copper layers, 43.1 x 60.6 mm, 41 parts (4 on the bottom side), 72 nets.

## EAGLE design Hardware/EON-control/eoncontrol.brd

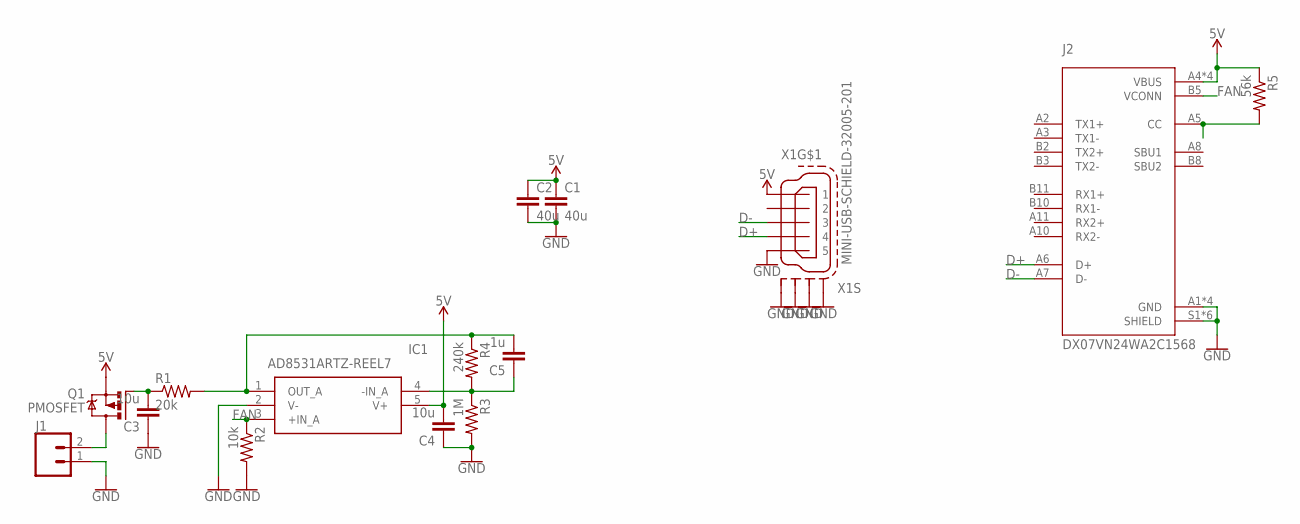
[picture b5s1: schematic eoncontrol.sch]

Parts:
C1, C2: 40u; C1206
C3, C4: 10u; 0603-C
C5: 1u; 0603-C
IC1: AD8531ARTZ-REEL7; SOT95P280X145-5N
J1: CONN_02; 1X02
J2: DX07VN24WA2C1568; JAE_DX07VN24WA2C1568
Q1: PMOSFET; SOT23
R1: 20k; 0603-R
R2: 10k; 0603-R
R3: 1M; 0603-R
R4: 240k; 0603-R
R5: 56k; 0603-R
X1: MINI-USB-SCHIELD-32005-201; 32005-201

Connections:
5V: C1.1, C2.1, C4.2, IC1.5 (V+), J2.A4 (VBUS), J2.A9 (VBUS), J2.B4 (VBUS), J2.B9 (VBUS), Q1.2 (S), R5.1, X1.1
D+: J2.A6 (D+), X1.4
D-: J2.A7 (D-), X1.3
FAN: IC1.3 (+IN_A), J2.B5 (VCONN), R2.1
GND: C1.2, C2.2, C3.1, C4.1, IC1.2 (V-), J1.1, J2.A1 (GND), J2.A12 (GND), J2.B1 (GND), J2.B12 (GND), J2.S1 (SHIELD), J2.S2 (SHIELD), J2.S3 (SHIELD), J2.S4 (SHIELD), J2.S5 (SHIELD), J2.S6 (SHIELD), R2.2, R3.2, X1.5, X1.M1 (S1), X1.M2 (S2), X1.M3 (S3), X1.M4 (S4)
unnamed: C3.2, Q1.1 (G), R1.1
unnamed: J1.2, Q1.3 (D)
unnamed: C5.1, IC1.4 (-IN_A), R3.1, R4.2
unnamed: C5.2, IC1.1 (OUT_A), R1.2, R4.1
unnamed: J2.A5 (CC), R5.2

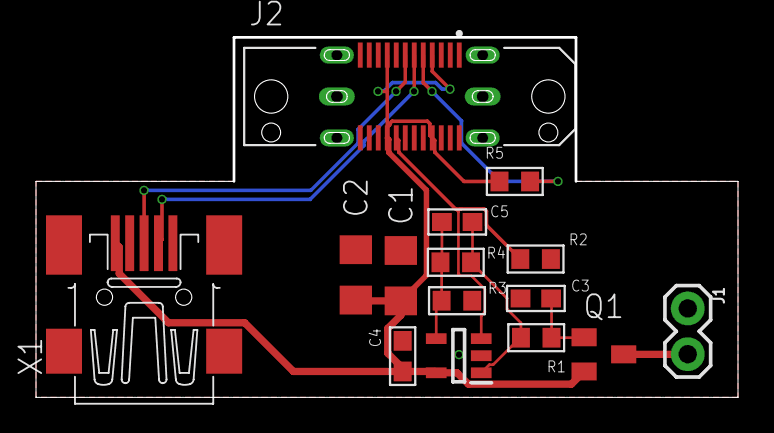
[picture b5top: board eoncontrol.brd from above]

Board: 2 copper layers, 39.0 x 20.0 mm, 15 parts (0 on the bottom side), 10 nets.

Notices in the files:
parts and their libraries:
interceptor: COPYRIGHT: Copyright (C) 2018 Accelerated Designs. All rights reserved
SparkFun-PowerSymbols: Licensing: Creative Commons ShareAlike 4.0 International - https://creativecommons.org/licenses/by-sa/4.0
